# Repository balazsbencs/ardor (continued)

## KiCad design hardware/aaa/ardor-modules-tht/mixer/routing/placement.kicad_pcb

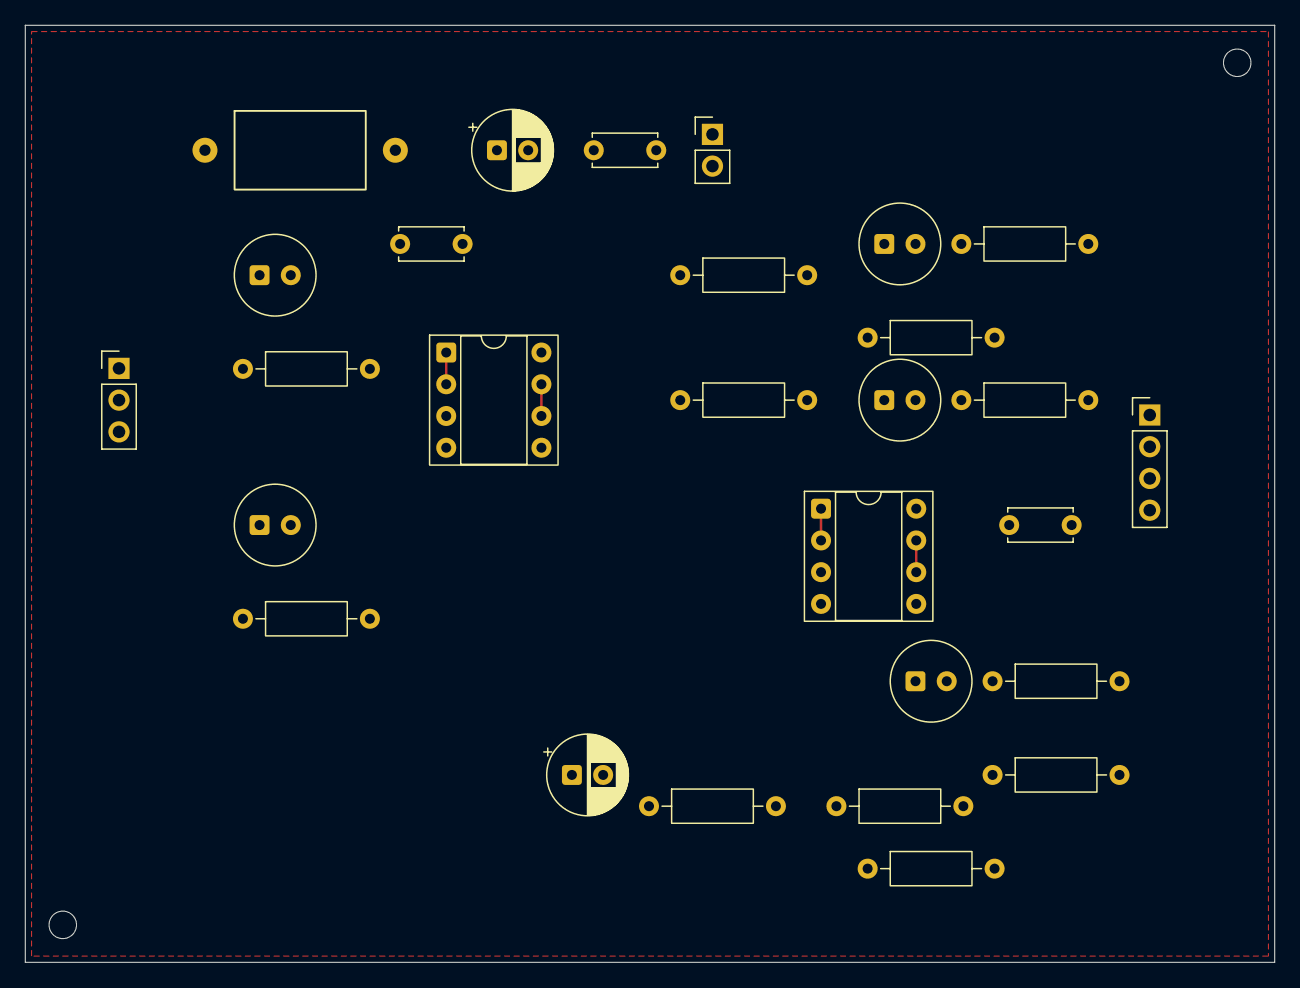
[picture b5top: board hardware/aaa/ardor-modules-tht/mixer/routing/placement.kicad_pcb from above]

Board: 2 copper layers, 100.0 x 75.0 mm, 30 parts (0 on the bottom side), 19 nets.

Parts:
C101: 22u / 25V polarized; CP_Radial_D6.3mm_P2.50mm
C102, C404, C405: 100n / 50V X7R; C_Disc_D5.0mm_W2.5mm_P5.00mm
C401, C402, C407, C408, C409: 10u / 25V BIPOLAR; CP_Bipolar_D6.3mm_P2.50mm
C403: 10u / 25V polarized; CP_Radial_D6.3mm_P2.50mm
FB101: 800R@100MHz / WE 7427501; Ferrite_WE_7427501_P15.24mm
H1, H2: MountingHole_2.2mm_M2
J101: 5V POWER INPUT; PinHeader_1x02_P2.54mm_Vertical
J102: STEREO AUDIO INPUT FROM SOURCE; PinHeader_1x03_P2.54mm_Vertical
J103: BUFFERED STEREO + MONO AUDIO OUTPUT; PinHeader_1x04_P2.54mm_Vertical
R401, R402, R410, R411, R412: 100kR / 1% 0.25W; R_Axial_DIN0207_L6.3mm_D2.5mm_P10.16mm_Horizontal
R403, R404, R405, R406: 10kR / 1% 0.25W; R_Axial_DIN0207_L6.3mm_D2.5mm_P10.16mm_Horizontal
R407, R408, R409: 100R / 1% 0.25W; R_Axial_DIN0207_L6.3mm_D2.5mm_P10.16mm_Horizontal
U401, U402: MCP6022-I/P; DIP-8_W7.62mm_Socket

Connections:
/+5V: FB101.1, J101.1
/+5V_A: C101.1, C102.1, C404.1, C405.1, FB101.2, R405.1, U401.8, U402.8
/GND: C101.2, C102.2, C403.2, C404.2, C405.2, J101.2, J102.2, J103.2, R406.2, R410.2, R411.2, R412.2, U401.4, U402.4
/VREF: R401.2, R402.2, U402.6, U402.7
unnamed: C407.2, R407.1, R410.1
unnamed: C408.2, R408.1, R411.1
unnamed: C409.2, R409.1, R412.1
unnamed: C401.1, J102.1
unnamed: C402.1, J102.3
unnamed: J103.1, R407.2
unnamed: J103.3, R408.2
unnamed: J103.4, R409.2
unnamed: C401.2, R401.1, U401.3
unnamed: C407.1, R403.1, U401.1, U401.2
unnamed: C402.2, R402.1, U401.5
unnamed: C408.1, R404.1, U401.6, U401.7
unnamed: R403.2, R404.2, U402.3
unnamed: C409.1, U402.1, U402.2
unnamed: C403.1, R405.2, R406.1, U402.5

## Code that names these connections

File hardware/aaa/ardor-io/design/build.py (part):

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 cp=L.p((cref,1),'1');path(L,(66.04,yy),cp);L.label(buf,(86.36,yy));L.joint((66.04,yy))
 unhook(L,cref,'2');unhook(L,rref,'1')
 path(L,L.p((cref,1),'2'),L.p((rref,1),'1'))
 ac='LINE_AC' if unit==1 else 'AMP_AC';L.label(ac,(144.78,yy))
unhook(L,'R501','1');path(L,(162.56,71.12),L.p(('R501',1),'1'));L.joint((162.56,71.12))
# line driver to relay NO (vertical top pin)
unhook(L,'R502','2');unhook(L,'K501','10')
path(L,L.p(('R502',1),'2'),(246.38,71.12),(246.38,55.88),(276.86,55.88),L.p(('K501',1),'10'))
L.label('LINE_DRIVE',(246.38,55.88))
# amp output and pulldown
for ref,pin in [('R505','2'),('R506','1'),('J502','1')]:unhook(L,ref,pin)
# move R506 below horizontal signal to avoid drawing through its body
# route output on a track above the pulldown, then down to the header.
path(L,L.p(('R505',1),'2'),(210.82,243.84),(210.82,228.6),(281.94,228.6),(281.94,243.84),L.p(('J502',1),'1'))
path(L,(243.84,228.6),L.p(('R506',1),'1'));L.joint((243.84,228.6));L.label('AMP_FEED',(266.7,228.6))
# Headphone coupling capacitors routed into the driver.
for cref,pn,net,xx in [('C601','4','HP_IN_R',121.92),('C602','1','HP_IN_L',134.62)]:
 unhook(H,cref,'2');unhook(H,'U601',pn)
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
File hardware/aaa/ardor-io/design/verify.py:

from pathlib import Path
import json,xml.etree.ElementTree as ET,hashlib,csv
import pymupdf as fitz
P=Path(__file__).resolve().parents[1]
expected=json.loads((P/'design/expected_nets.json').read_text())
r=ET.parse(P/'verification/netlist.xml')
actual={n.attrib['ref']+'.'+n.attrib['pin']:net.attrib['name'].rsplit('/',1)[-1] for net in r.findall('.//nets/net') for n in net.findall('node')}
errors=[f'{pin}: expected {net}, got {actual.get(pin)}' for pin,net in expected.items() if not pin.startswith('#') and actual.get(pin)!=net]
# Deliberate circuit invariants, independent of the generated expected-net map.
checks={
 'Pi UART RX uses GPIO15, pin 10':actual['J101.10']=='MIDI_RX',
 'Pi headphone enable uses GPIO17, pin 11':actual['J101.11']=='HP_ENABLE',
 'Pi line enable uses GPIO22, pin 15':actual['J101.15']=='LINE_ENABLE',
 'Codec button GPIO27 is not borrowed':actual.get('J101.13','').startswith('unconnected-'),
 'MIDI output is not pulled up to 5V':actual['R202.1']=='+3V3_PI',
 'MIDI LED reverse diode correct':actual['D201.1']==actual['U201.1'] and actual['D201.2']==actual['U201.2'],
 'MIDI differential TVS across DIN4/5':{actual['D202.1'],actual['D202.2']}=={'MIDI_4','MIDI_5'},
 'ADC address grounded, 0x48':actual['U301.1']=='GND',
 'Both ADC channels have upper and lower clamps':all(actual[d+'.1']=='+3V3_ADC' for d in ['D303','D305']) and all(actual[d+'.2']=='GND' for d in ['D304','D306']),
 'Line relay NC grounds jack; NO carries signal':actual['K501.1']=='GND' and actual['K501.10']=='LINE_DRIVE' and actual['K501.5']==actual['K501.6']=='LINE_JACK',
 'Line capacitor polarity faces biased output':actual['C501.1']=='LINE_BUF',
 'Separate line/amp buffers':actual['U501.1']=='LINE_BUF' and actual['U501.7']=='AMP_BUF',
 'Headphone charge-pump reservoir nets distinct from 5V':actual['U601.12']=='HPVDD' and actual['U601.8']=='HPVSS' and actual['U601.14']=='+5V_A',
 'Headphone flying capacitor across CPP/CPN':{actual['C607.1'],actual['C607.2']}=={'CPP','CPN'},
 'Headphone gain -6dB and inputs single-ended':all(actual['U601.'+n]=='GND' for n in ['2','3','6','7']),
 'Headphone ground and thermal pad connected':all(actual['U601.'+n]=='GND' for n in ['10','15','17']),
 'No short between AUX L and R':actual['J102.1']!=actual['J102.3'],
 'ADC and audio rails distinct':actual['U301.8']!=actual['U601.14'],
}
errors += [k for k,v in checks.items() if not v]
assert not errors,'\n'.join(errors)
report=['Ardor Rev A connectivity verification','',f'PASS: {sum(not k.startswith("#") for k in expected)} assigned physical pin connections match the exported KiCad netlist.',f'PASS: {len(checks)} independent circuit invariants.','']+[('PASS: '+k) for k in checks]
report+=['','ERC: see erc.rpt. No suppressed ERC rules or exclusions.','No hardware, SPICE, audio performance or assembled-product ESD qualification has been performed.']
(P/'verification/connectivity-audit.txt').write_text('\n'.join(report)+'\n')
doc=fitz.open(P/'Ardor_IO.pdf');assert len(doc)==6
for i,p in enumerate(doc):p.get_pixmap(matrix=fitz.Matrix(1.35,1.35)).save(P/f'verification/page-{i+1}.png')
print('\n'.join(report[:5]))
